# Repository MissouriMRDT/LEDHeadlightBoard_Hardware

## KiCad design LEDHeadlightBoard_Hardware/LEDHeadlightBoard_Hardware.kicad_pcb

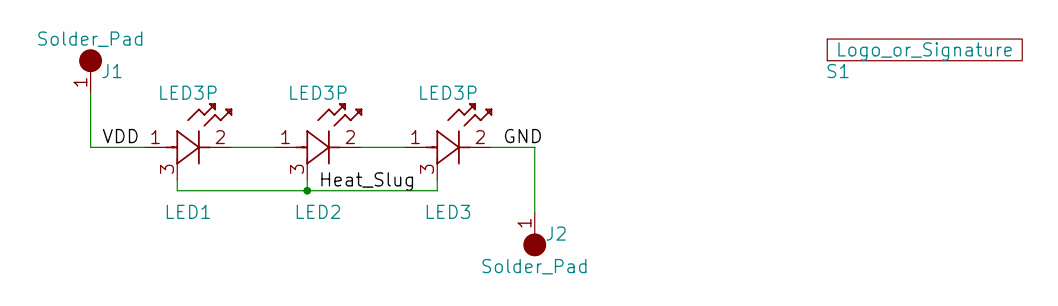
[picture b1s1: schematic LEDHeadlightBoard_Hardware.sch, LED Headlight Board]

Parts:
J1, J2: Solder_Pad; Solder_Pad_5mmX3mm
LED1, LED2, LED3: LED3P; LED_CREE_XLAMP_XPG
S1: Logo_or_Signature; MRDT_Logo_10mm

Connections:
/GND: J2.1, LED3.2 (Cathode)
/Heat_Slug: LED1.3 (Heat_Dissipation), LED2.3 (Heat_Dissipation), LED3.3 (Heat_Dissipation)
/VDD: J1.1, LED1.1 (Anode)
unnamed: LED1.2 (Cathode), LED2.1 (Anode)
unnamed: LED2.2 (Cathode), LED3.1 (Anode)

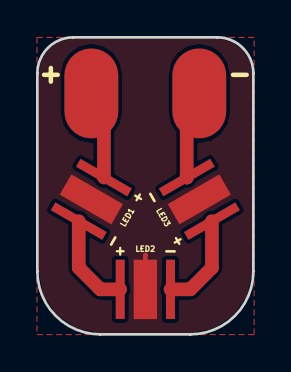
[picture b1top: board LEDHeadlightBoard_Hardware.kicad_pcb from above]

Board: 2 copper layers, 12.0 x 16.5 mm, 6 parts (1 on the bottom side), 5 nets.

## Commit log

2018-03-16 Schematic Complete
    Footprints are assigned to devices and Netlist was generated. Ready to start layout.
2018-03-20 Board Complete for Cree XLamp XP-G2
    EasyEDA does not like the gerbs, need to figure that out. May have to do with how small the board is.
2018-03-24 Rev.1 Layout Finished
    Meant for use with Cree XLamp XP-G2 LEDs (XPGBWT-L1-0000-00H53)
